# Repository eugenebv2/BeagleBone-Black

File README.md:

# BeagleBone-Black

   Static hostname: BeagleBone   
         Icon name: computer-embedded         
           Chassis: embedded           
        Machine ID: 454bbe9c893a4e109cb1317d7bde7228        
           Boot ID: fe954291367040828aac4ce6702a8503           
  Operating System: Debian GNU/Linux 11 (bullseye)  
            Kernel: Linux 5.10.168-ti-r73            
      Architecture: arm
      
With Grove Base Cape

<hr>

Install Libmosquitto. ( sudo apt-get install mosquitto mosquitto-dev libmosquitto* ) Include mosquitto service , but not use the service. Refenence Libmosquitto Functions from https://mosquitto.org/api/files/mosquitto-h.html 

git Clone from <a href="https://github.com/positronic57/MQTT_examples_with_libmosquito" target="_blank"> MQTT_examples_with_libmosquito </a>. And test mqtt_sub example. 

Base on this change the i2c/testbmp280 to send data using MQTT publish.

<hr>

![alt text][def1]

[def1]: images/IMG_4914.jpg

![alt text][def2]

[def2]: images/IMG_4915.jpg

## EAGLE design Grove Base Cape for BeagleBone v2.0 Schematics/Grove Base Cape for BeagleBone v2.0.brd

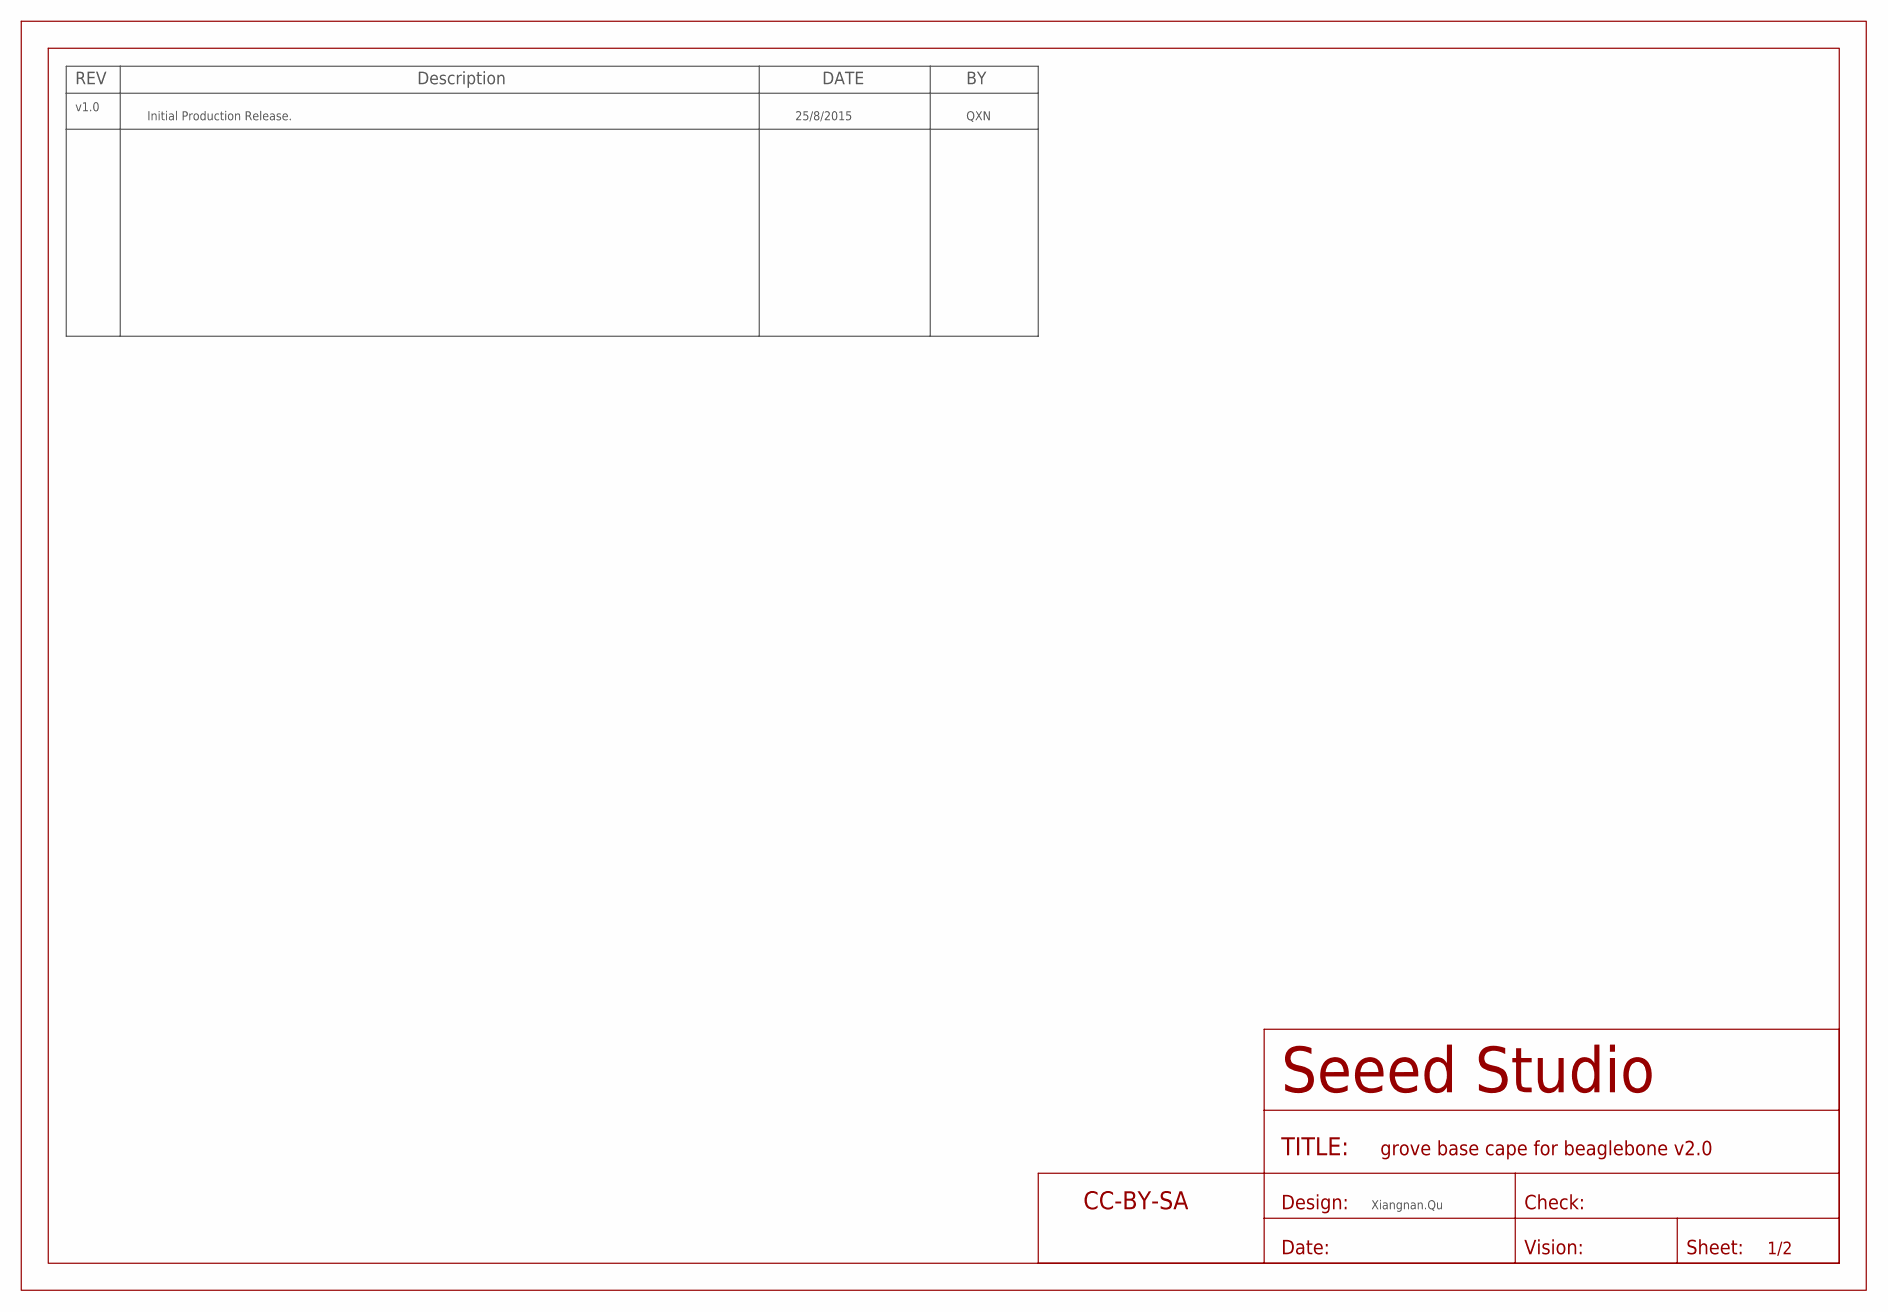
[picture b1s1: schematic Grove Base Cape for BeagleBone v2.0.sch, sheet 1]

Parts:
FR1: SEEEDSTUDIO-OPEN-SCH-FRAME; SEEEDSTUDIO-PCB-FRAME

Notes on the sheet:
REV
Description
DATE
v1.0
Initial Production Release.
25/8/2015
QXN
Xiangnan.Qu

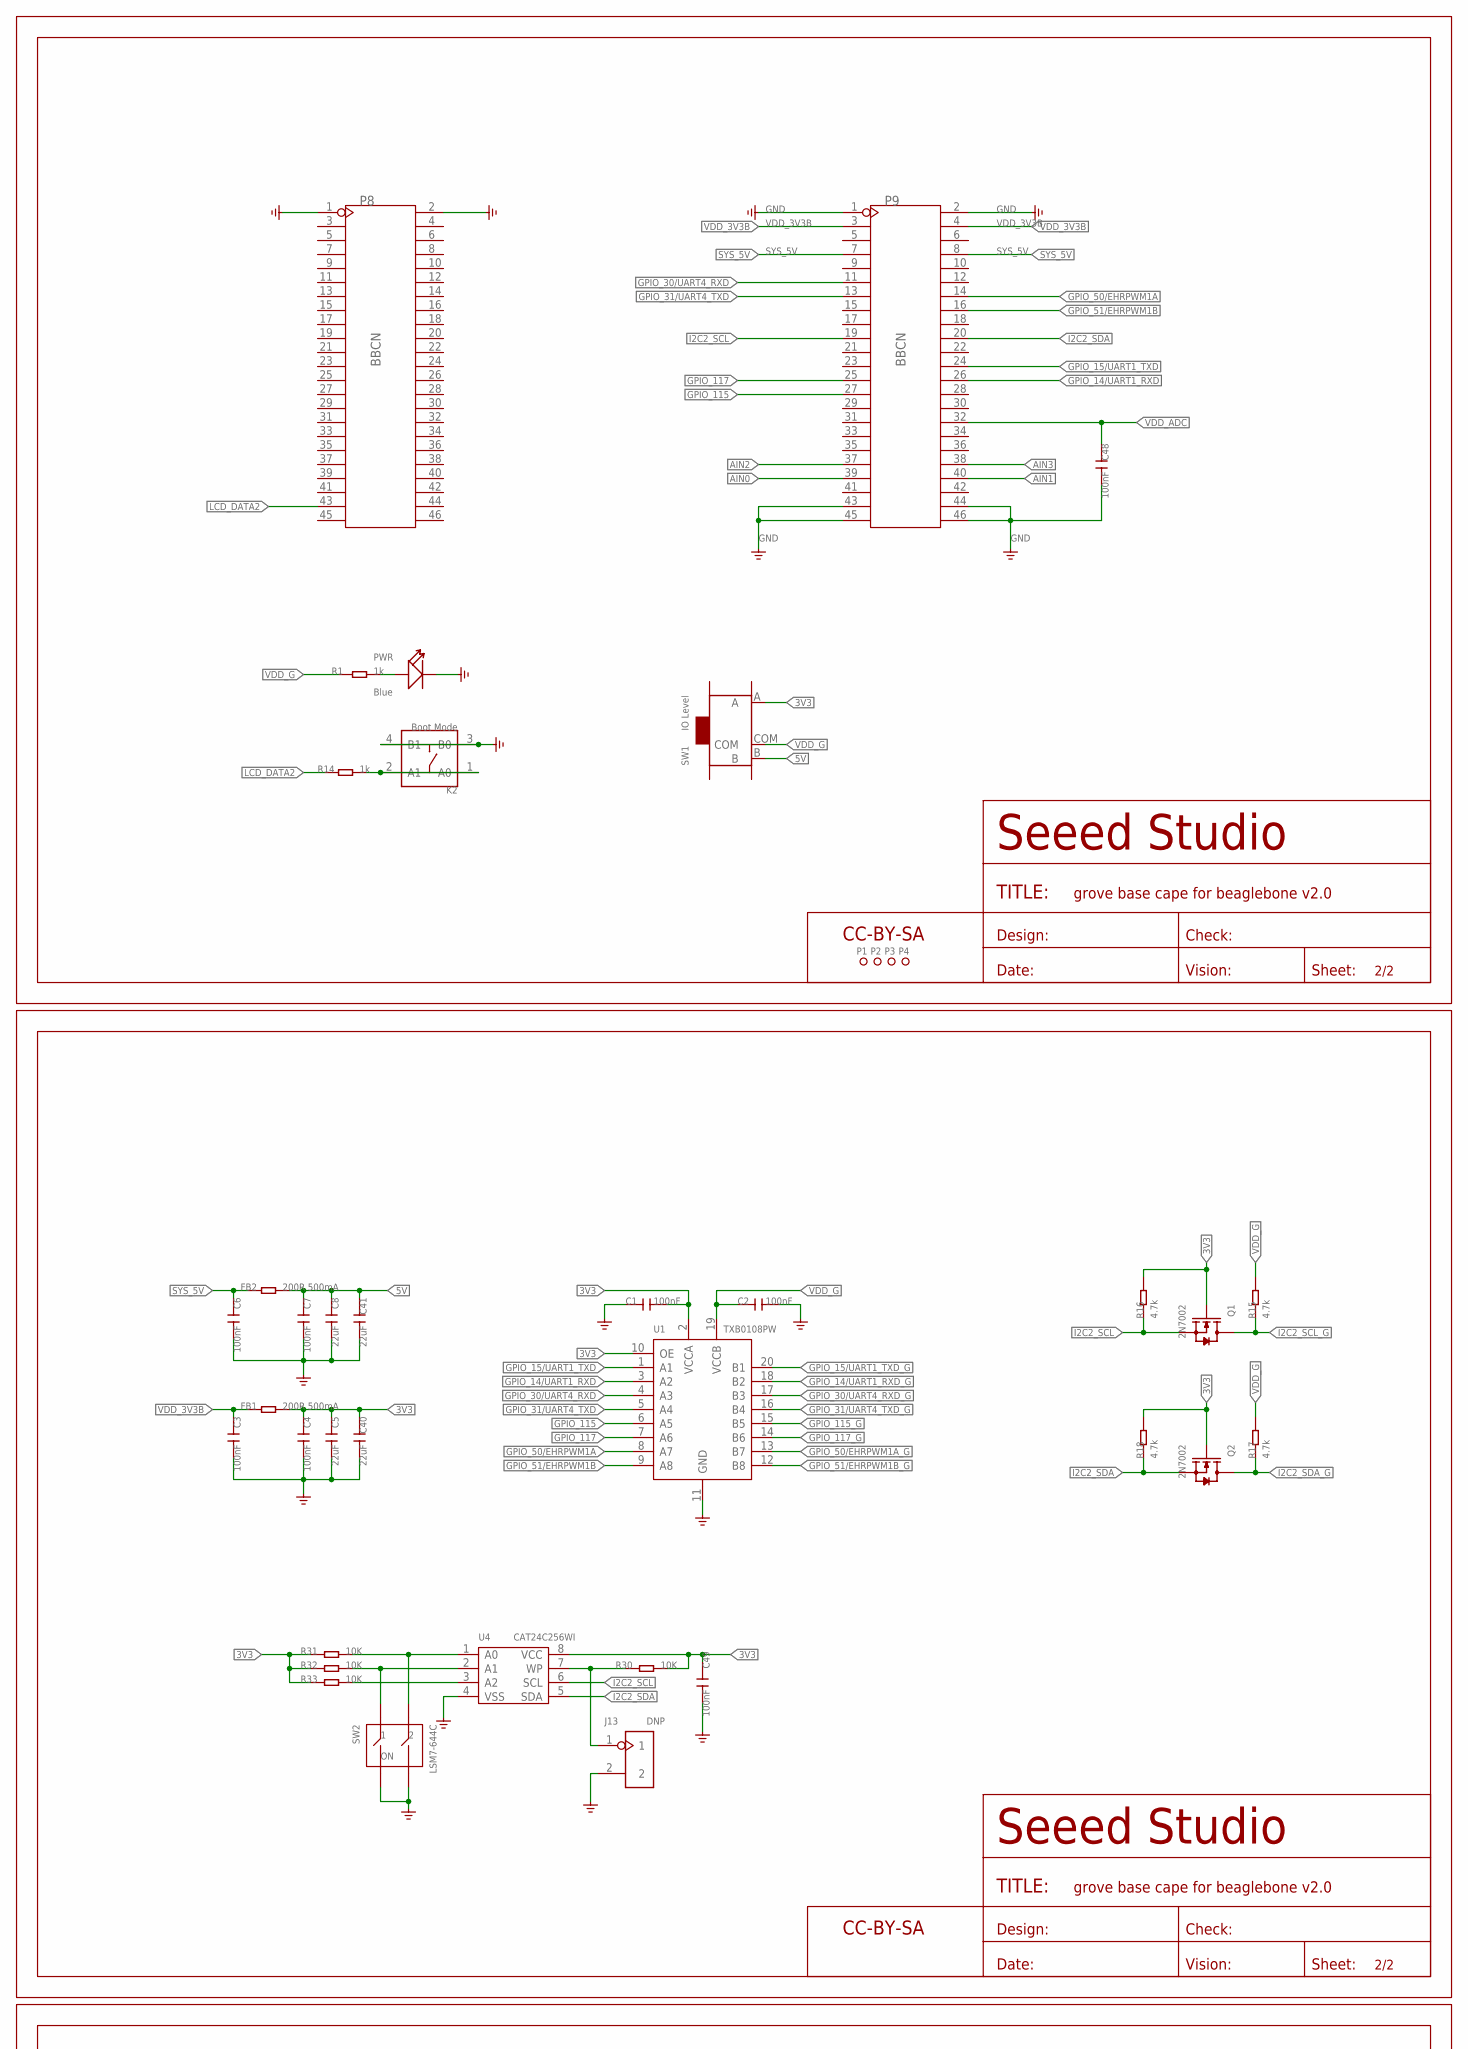
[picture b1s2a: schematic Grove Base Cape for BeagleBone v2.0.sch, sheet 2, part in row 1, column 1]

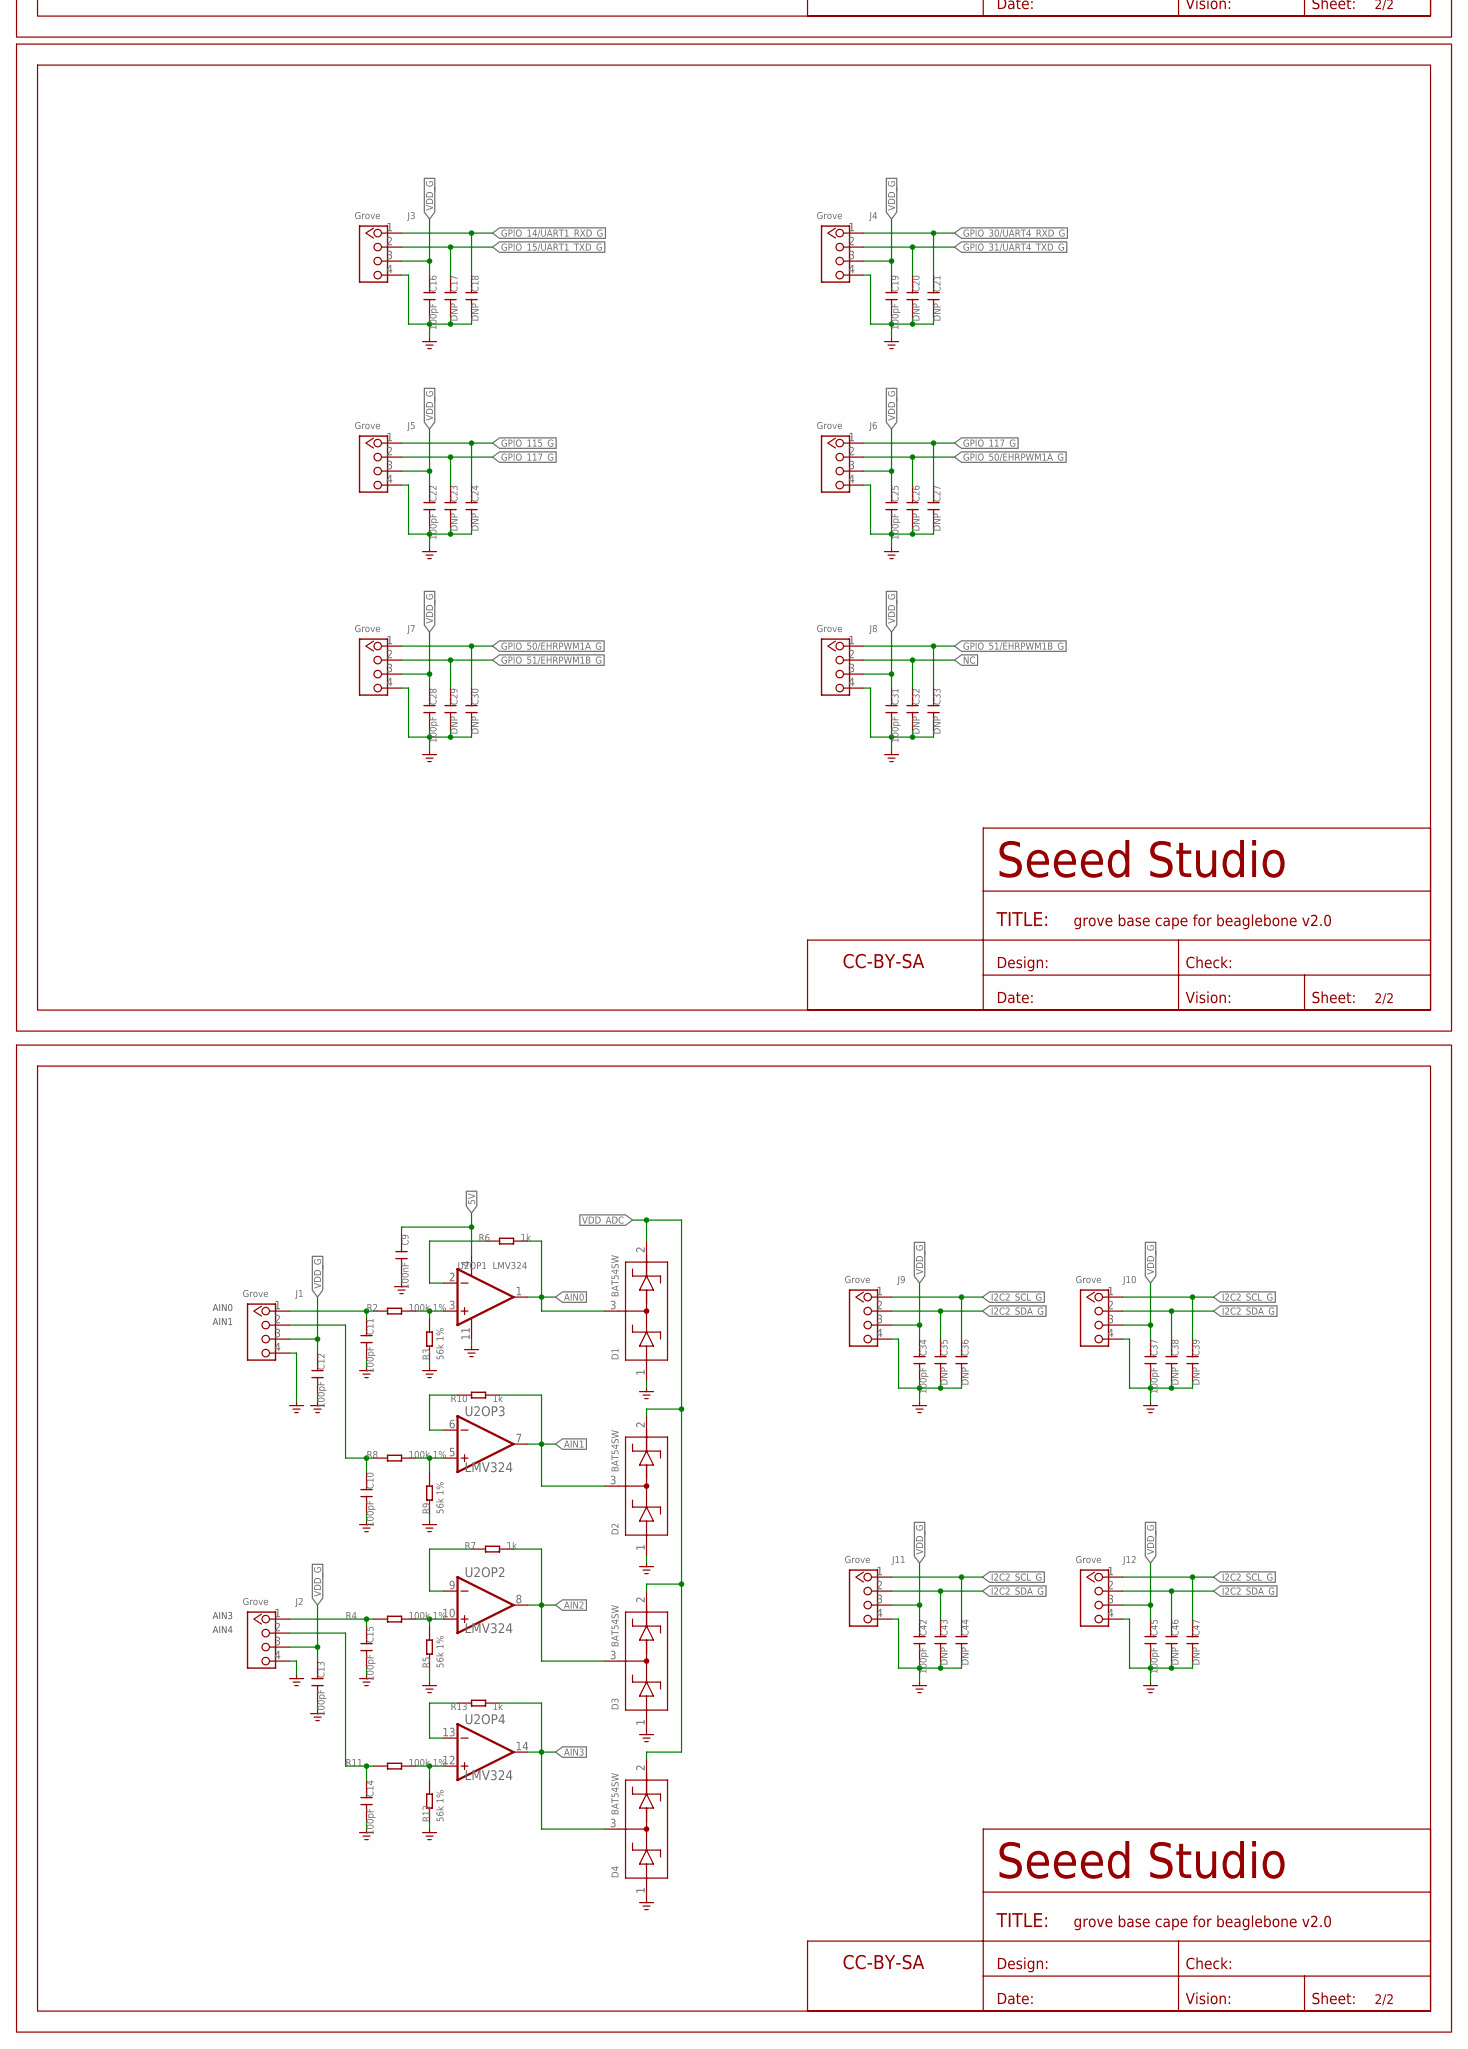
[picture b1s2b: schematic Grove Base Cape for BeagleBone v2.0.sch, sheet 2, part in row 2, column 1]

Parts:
C1, C2, C3, C4, C6, C7, C9, C48, C49: 100nF; C0402
C5, C8, C40, C41: 22uF; C0805
C10, C11, C12, C13, C14, C15, C16, C19, C22, C25, C28, C31, C34, C37, C42, C45: 100pF; C0402
C17, C18, C20, C21, C23, C24, C26, C27, C29, C30, C32, C33, C35, C36, C38, C39, C43, C44, C46, C47: DNP; C0402
D1, D2, D3, D4: BAT54SW; SOT-23
FB1, FB2: 200R 500mA; R0603
FR2, FR3, FR4, FR5: SEEEDSTUDIO-OPEN-SCH-FRAME; SEEEDSTUDIO-PCB-FRAME
J1, J2, J3, J4, J5, J6, J7, J8, J9, J10, J11, J12: Grove; HW4-2.0
J13: DNP; H2-1.5
K2: Boot Mode; SW4P-SMD-4.5X3.2X2.5MM
P1, P2, P3, P4: MARK-1.0'ANNULAR'; ROUND-MARK-1.0
P8, P9: BBCN; 2X23P-2.54
PWR: Blue; LED-0402
Q1, Q2: 2N7002; SOT-23
R1, R6, R7, R10, R13, R14: 1k; R0402
R2, R4, R8, R11: 100k 1%; R0402
R3, R5, R9, R12: 56k 1%; R0402
R15, R16, R17, R18: 4.7k; R0402
R30, R31, R32, R33: 10K; R0402
SW1: IO Level; SW7-SMD-L6.7X2.7X3.2MM
SW2: LSM7-644C; SW4-SMD-5.08X6.8X3.3MM
U1: TXB0108PW; TSSOP20-0.65-6.5X4.4MM
U2: LMV324; TSSOP14-0.65-5X4.4MM
U4: CAT24C256WI; SOIC8-1.27-5X4MM

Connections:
3V3: C1.2, C4.1, C5.1, C40.1, C49.2, FB1.2, Q1.1 (G), Q2.1 (G), R16.2, R18.2, R30.1, R31.2, R32.2, R33.2, SW1.A, U1.2 (VCCA), U1.10 (OE), U4.8 (VCC)
5V: C7.1, C8.1, C9.1, C41.1, FB2.2, SW1.B, U2.4 (V+)
AIN0: D1.3, P9.39, R6.2, U2.1 (OUT)
AIN1: D2.3, P9.40, R10.2, U2.7 (OUT)
AIN2: D3.3, P9.37, R7.2, U2.8 (OUT)
AIN3: D4.3, P9.38, R13.2, U2.14 (OUT)
GND: C1.1, C2.2, C3.2, C4.2, C5.2, C6.2, C7.2, C8.2, C9.2, C10.2, C11.2, C12.2, C13.2, C14.2, C15.2, C16.2, C17.2, C18.2, C19.2, C20.2, C21.2, C22.2, C23.2, C24.2, C25.2, C26.2, C27.2, C28.2, C29.2, C30.2, C31.2, C32.2, C33.2, C34.2, C35.2, C36.2, C37.2, C38.2, C39.2, C40.2, C41.2, C42.2, C43.2, C44.2, C45.2, C46.2, C47.2, C48.2, C49.1, D1.1, D2.1, D3.1, D4.1, J1.4, J2.4, J3.4, J4.4, J5.4, J6.4, J7.4, J8.4, J9.4, J10.4, J11.4, J12.4, J13.2, K2.3 (B0), K2.4 (B1), P8.1, P8.2, P9.1, P9.2, P9.43, P9.44, P9.45, P9.46, PWR.-, R3.1, R5.1, R9.1, R12.1, SW2.3, SW2.4, U1.11 (GND), U2.11 (V-), U4.4 (VSS)
GPIO_14/UART1_RXD: P9.26, U1.3 (A2)
GPIO_14/UART1_RXD_G: C18.1, J3.1, U1.18 (B2)
GPIO_15/UART1_TXD: P9.24, U1.1 (A1)
GPIO_15/UART1_TXD_G: C17.1, J3.2, U1.20 (B1)
GPIO_30/UART4_RXD: P9.11, U1.4 (A3)
GPIO_30/UART4_RXD_G: C21.1, J4.1, U1.17 (B3)
GPIO_31/UART4_TXD: P9.13, U1.5 (A4)
GPIO_31/UART4_TXD_G: C20.1, J4.2, U1.16 (B4)
GPIO_50/EHRPWM1A: P9.14, U1.8 (A7)
GPIO_50/EHRPWM1A_G: C26.1, C30.1, J6.2, J7.1, U1.13 (B7)
GPIO_51/EHRPWM1B: P9.16, U1.9 (A8)
GPIO_51/EHRPWM1B_G: C29.1, C33.1, J7.2, J8.1, U1.12 (B8)
GPIO_115: P9.27, U1.6 (A5)
GPIO_115_G: C24.1, J5.1, U1.15 (B5)
GPIO_117: P9.25, U1.7 (A6)
GPIO_117_G: C23.1, C27.1, J5.2, J6.1, U1.14 (B6)
I2C2_SCL: P9.19, Q1.2 (S), R16.1, U4.6 (SCL)
I2C2_SCL_G: C36.1, C39.1, C44.1, C47.1, J9.1, J10.1, J11.1, J12.1, Q1.3 (D), R15.1
I2C2_SDA: P9.20, Q2.2 (S), R18.1, U4.5 (SDA)
I2C2_SDA_G: C35.1, C38.1, C43.1, C46.1, J9.2, J10.2, J11.2, J12.2, Q2.3 (D), R17.1
LCD_DATA2: P8.43, R14.1
unnamed: R31.1, SW2.2, U4.1 (A0)
unnamed: R32.1, SW2.1, U4.2 (A1)
unnamed: K2.1 (A0), K2.2 (A1), R14.2
unnamed: PWR.+, R1.2
unnamed: R2.2, R3.2, U2.3 (IN+)
unnamed: R4.2, R5.2, U2.10 (IN+)
unnamed: C11.1, J1.1, R2.1
unnamed: R6.1, U2.2 (IN-)
unnamed: J13.1, R30.2, U4.7 (WP)
unnamed: C15.1, J2.1, R4.1
unnamed: R7.1, U2.9 (IN-)
unnamed: R33.1, U4.3 (A2)
unnamed: C14.1, J2.2, R11.1
unnamed: R11.2, R12.2, U2.12 (IN+)
unnamed: C10.1, J1.2, R8.1
unnamed: R8.2, R9.2, U2.5 (IN+)
unnamed: R10.1, U2.6 (IN-)
unnamed: R13.1, U2.13 (IN-)
NC: C32.1, J8.2
SYS_5V: C6.1, FB2.1, P9.7, P9.8
VDD_3V3B: C3.1, FB1.1, P9.3, P9.4
VDD_ADC: C48.1, D1.2, D2.2, D3.2, D4.2, P9.32
VDD_G: C2.1, C12.1, C13.1, C16.1, C19.1, C22.1, C25.1, C28.1, C31.1, C34.1, C37.1, C42.1, C45.1, J1.3, J2.3, J3.3, J4.3, J5.3, J6.3, J7.3, J8.3, J9.3, J10.3, J11.3, J12.3, R1.1, R15.2, R17.2, SW1.COM, U1.19 (VCCB)

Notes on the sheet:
AIN0
AIN1
AIN3
AIN4

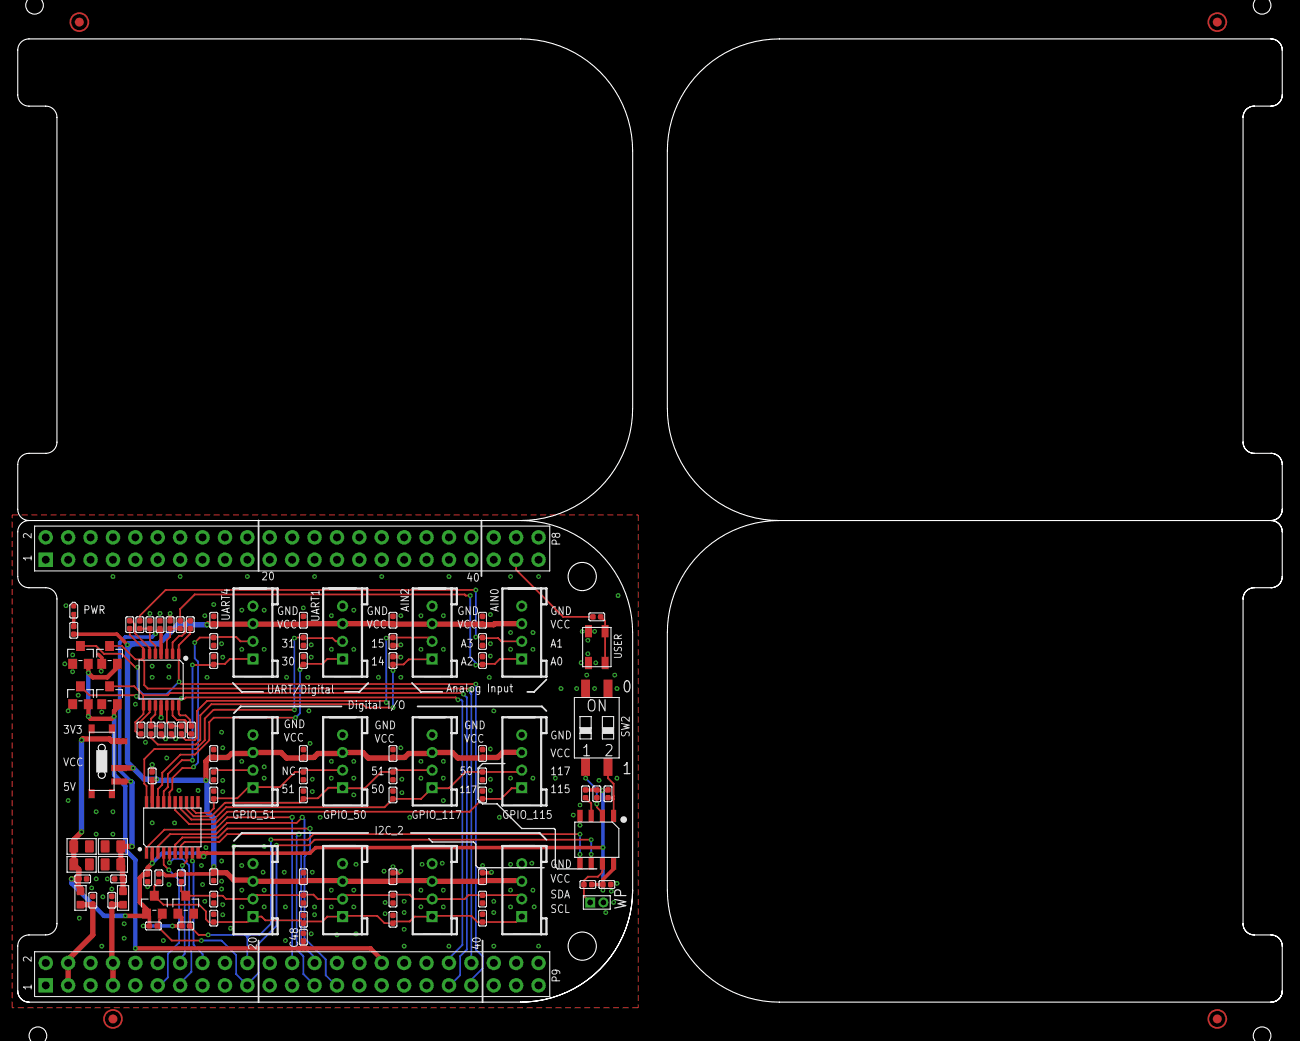
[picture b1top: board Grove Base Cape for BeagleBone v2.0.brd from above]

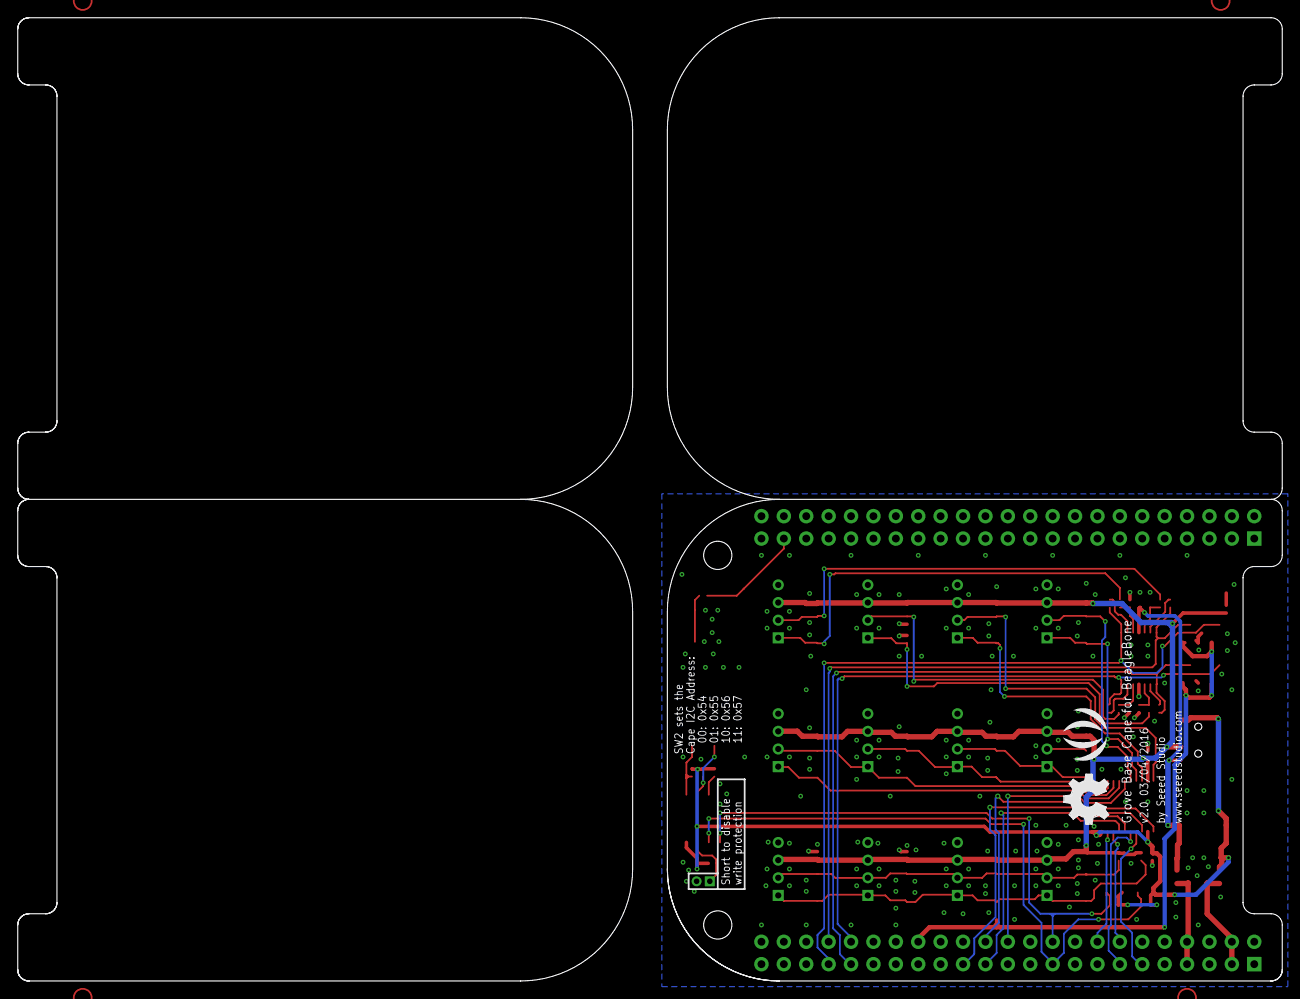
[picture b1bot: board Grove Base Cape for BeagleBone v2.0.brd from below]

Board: 2 copper layers, 69.7 x 109.2 mm, 114 parts (2 on the bottom side), 51 nets.

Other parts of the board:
U$16: SEEED-SILK-280*268MIL
U$18: OSHW_FILLX200_NOTEXT
U$26, U$27: HOLE-3.2/7.0

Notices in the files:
parts and their libraries:
moudle-new: This work is licensed under the Creative Commons Attribution 4.0 International License.
To view a copy of this license,visit:
http://creativecommons.org/licenses/by-sa/4.0
moudle-new: CC-BY-SA
